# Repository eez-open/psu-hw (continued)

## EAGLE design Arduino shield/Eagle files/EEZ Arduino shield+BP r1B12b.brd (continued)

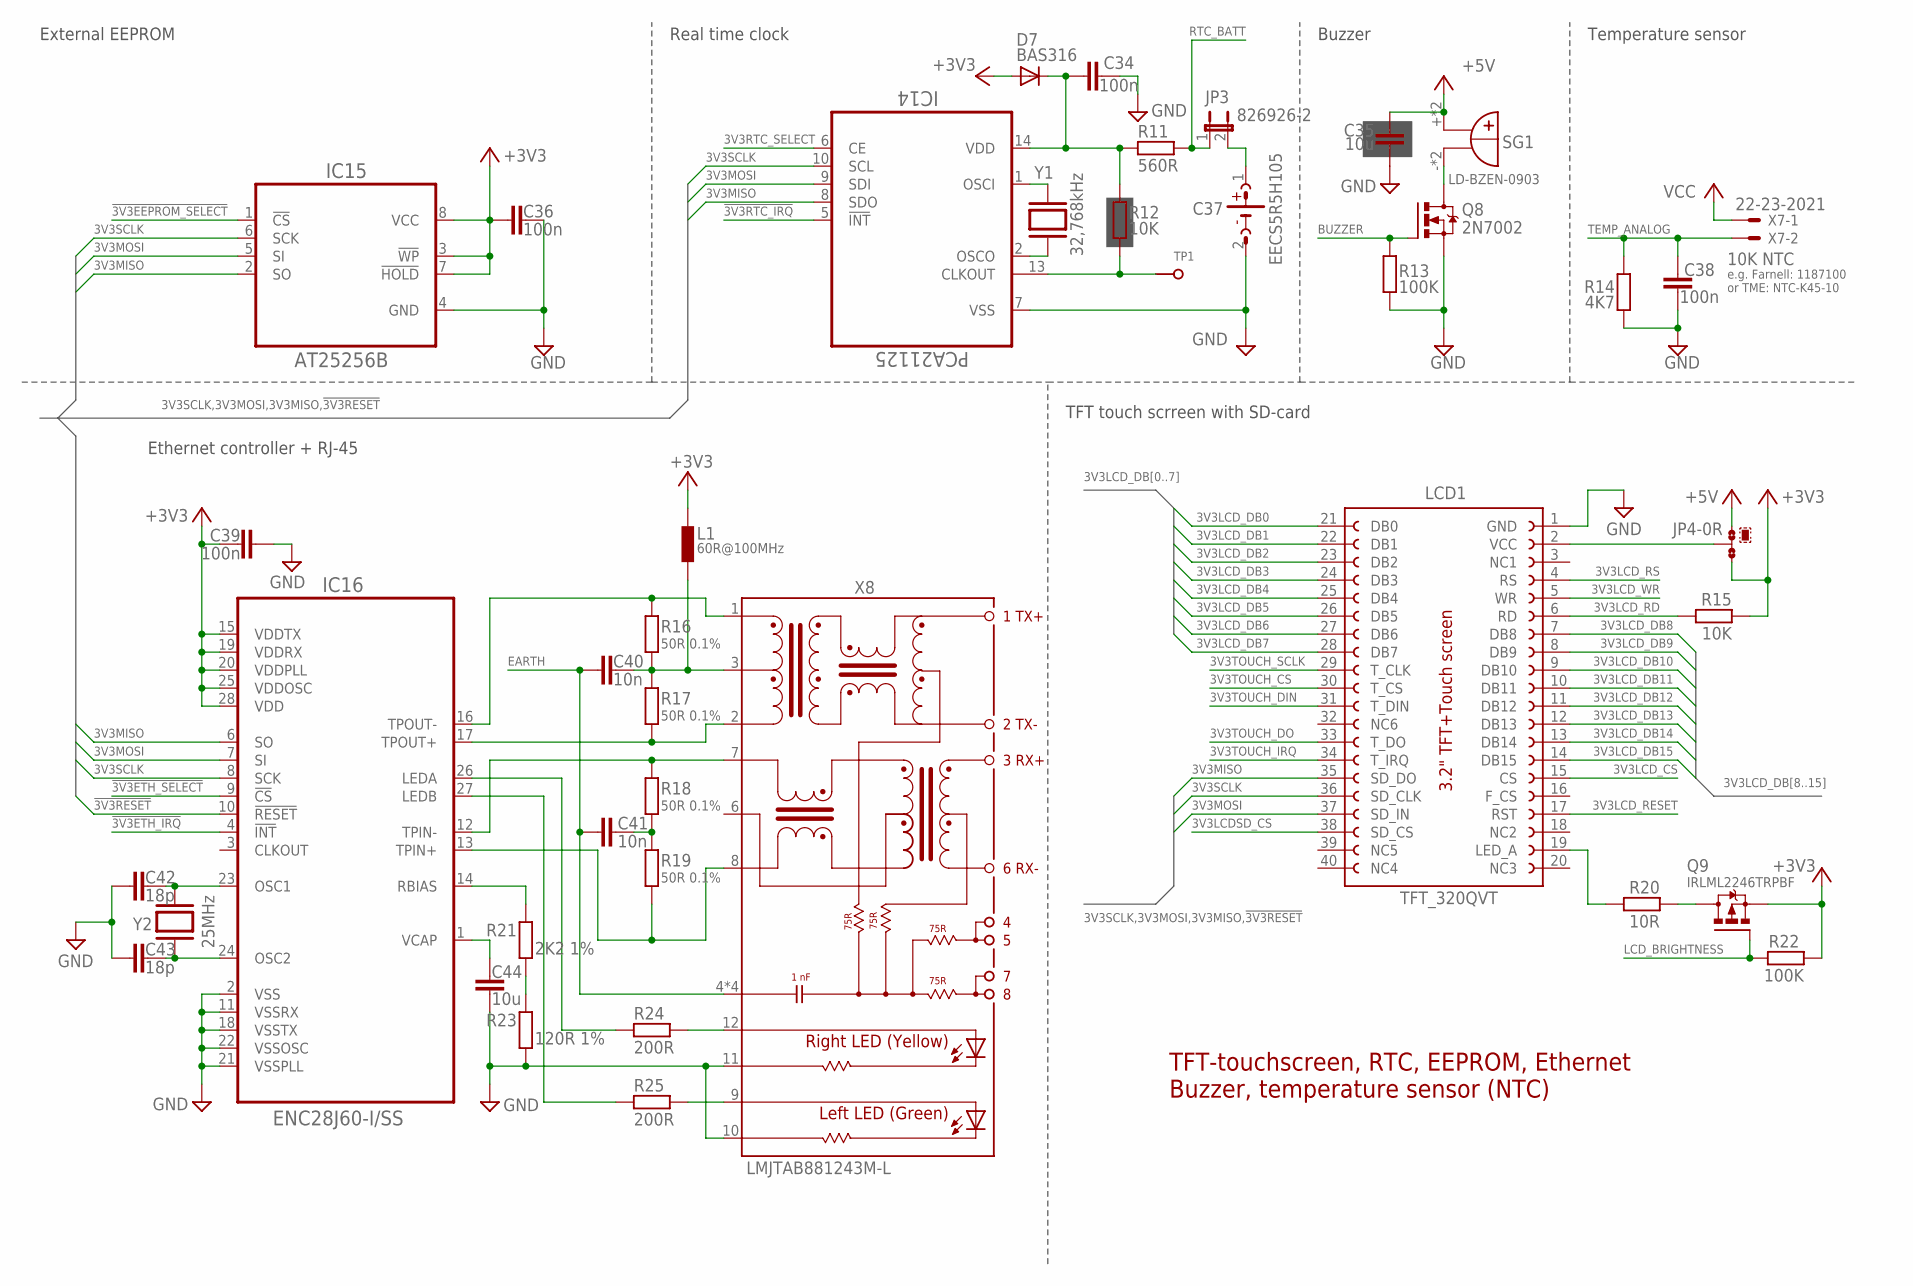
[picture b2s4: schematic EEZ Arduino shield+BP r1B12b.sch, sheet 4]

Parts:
C34, C36, C38, C39: 100n; C0603
C35, C44: 10u; C1206
C37: EECS5R5H105; SG-R20MM
C40, C41: 10n; C1206
C42, C43: 18p; C0805
D7: BAS316; SOD323-W
IC14: PCA21125; SOP65P640X120-14N
IC15: AT25256B; SOIC127P600X175-8N
IC16: ENC28J60-I/SS; SOP65P780X200-28N
JP3: 826926-2; JP1
JP4: 0R-JUMPA; A0R-JMP
L1: 60R@100MHz; BEAD0603
LCD1: TFT_320QVT; LCD_TFT_320QVT_MIRROR
Q8: 2N7002; SOT103P240X110-3N
Q9: IRLML2246TRPBF; SOT95P237X112-3N
R11: 560R; R0805
R12, R15: 10K; R0805
R13, R22: 100K; R0805
R14: 4K7; R0805
R16, R17, R18, R19: 50R 0.1%; R0805
R20: 10R; R0805
R21: 2K2 1%; R0805
R23: 120R 1%; R0805
R24, R25: 200R; R0805
SG1: LD-BZEN-0903; BUZZER
TP1: PCB_TEST_TABSHIELD; PCB_SHIELD_TAB
X7: 22-23-2021; MPN 22-23-2021
X8: LMJTAB881243M-L; RJ45-TRAFO-LED
Y1: 32,768kHz; R26_XTAL
Y2: 25MHz; HC-49/4H

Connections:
3V3LCDSD_CS: LCD1.38 (SD_CS); also elsewhere on the board
3V3LCD_CS: LCD1.15 (CS); also elsewhere on the board
3V3LCD_DB0: LCD1.21 (DB0); also elsewhere on the board
3V3LCD_DB1: LCD1.22 (DB1); also elsewhere on the board
3V3LCD_DB2: LCD1.23 (DB2); also elsewhere on the board
3V3LCD_DB3: LCD1.24 (DB3); also elsewhere on the board
3V3LCD_DB4: LCD1.25 (DB4); also elsewhere on the board
3V3LCD_DB5: LCD1.26 (DB5); also elsewhere on the board
3V3LCD_DB6: LCD1.27 (DB6); also elsewhere on the board
3V3LCD_DB7: LCD1.28 (DB7); also elsewhere on the board
3V3LCD_DB8: LCD1.7 (DB8); also elsewhere on the board
3V3LCD_DB9: LCD1.8 (DB9); also elsewhere on the board
3V3LCD_DB10: LCD1.9 (DB10); also elsewhere on the board
3V3LCD_DB11: LCD1.10 (DB11); also elsewhere on the board
3V3LCD_DB12: LCD1.11 (DB12); also elsewhere on the board
3V3LCD_DB13: LCD1.12 (DB13); also elsewhere on the board
3V3LCD_DB14: LCD1.13 (DB14); also elsewhere on the board
3V3LCD_DB15: LCD1.14 (DB15); also elsewhere on the board
3V3LCD_RD: LCD1.6 (RD), R15.1
3V3LCD_RESET: LCD1.17 (RST); also elsewhere on the board
3V3LCD_RS: LCD1.4 (RS); also elsewhere on the board
3V3LCD_WR: LCD1.5 (WR); also elsewhere on the board
3V3MISO: IC14.8 (SDO), IC15.2 (SO), IC16.6 (SO), LCD1.35 (SD_DO); also elsewhere on the board
3V3MOSI: IC14.9 (SDI), IC15.5 (SI), IC16.7 (SI), LCD1.37 (SD_IN); also elsewhere on the board
3V3RTC_SELECT: IC14.6 (CE); also elsewhere on the board
3V3SCLK: IC14.10 (SCL), IC15.6 (SCK), IC16.8 (SCK), LCD1.36 (SD_CLK); also elsewhere on the board
3V3TOUCH_CS: LCD1.30 (T_CS); also elsewhere on the board
3V3TOUCH_DIN: LCD1.31 (T_DIN); also elsewhere on the board
3V3TOUCH_DO: LCD1.33 (T_DO); also elsewhere on the board
3V3TOUCH_IRQ: LCD1.34 (T_IRQ); also elsewhere on the board
3V3TOUCH_SCLK: LCD1.29 (T_CLK); also elsewhere on the board
!3V3EEPROM_SELECT: IC15.1 (!CS); also elsewhere on the board
!3V3ETH_IRQ: IC16.4 (!INT); also elsewhere on the board
!3V3ETH_SELECT: IC16.9 (!CS); also elsewhere on the board
!3V3RESET: IC16.10 (!RESET); also elsewhere on the board
!3V3RTC_IRQ: IC14.5 (!INT); also elsewhere on the board
+3V3: C36.1, C39.1, D7.A, IC15.3 (!WP), IC15.7 (!HOLD), IC15.8 (VCC), IC16.15 (VDDTX), IC16.19 (VDDRX), IC16.20 (VDDPLL), IC16.25 (VDDOSC), IC16.28 (VDD), JP4.3, L1.P$2 (2), Q9.2 (S), R15.2, R22.2; also elsewhere on the board
+5V: C35.2, JP4.1, SG1.+, SG1.+B (+); also elsewhere on the board
BUZZER: Q8.1 (G), R13.2; also elsewhere on the board
EARTH: C40.2, C41.2, X8.4 (SH), X8.5 (SH), X8.SH1 (SH), X8.SH2 (SH); also elsewhere on the board
ETH_IN+: IC16.13 (TPIN+), R19.1, X8.8 (RD-)
ETH_IN-: IC16.12 (TPIN-), R18.2, X8.7 (RD+)
ETH_LEDA: IC16.26 (LEDA), R24.1
ETH_LEDB: IC16.27 (LEDB), R25.1
ETH_OUT+: IC16.17 (TPOUT+), R17.1, X8.2 (TD-)
ETH_OUT-: IC16.16 (TPOUT-), R16.2, X8.1 (TD+)
GND: C34.1, C35.1, C36.2, C37.2 (-), C38.1, C39.2, C42.2, C43.2, C44.1, IC14.7 (VSS), IC15.4 (GND), IC16.2 (VSS), IC16.11 (VSSRX), IC16.18 (VSSTX), IC16.21 (VSSPLL), IC16.22 (VSSOSC), LCD1.1 (GND), Q8.2 (S), R13.1, R14.2, R23.2, X8.10 (GREEN-C), X8.11 (YELLOW-C); also elsewhere on the board
LCD_BRIGHTNESS: Q9.1 (G), R22.1; also elsewhere on the board
LED_A: LCD1.19 (LED_A), R20.2
unnamed: JP4.2, LCD1.2 (VCC)
unnamed: Q9.3 (D), R20.1
unnamed: IC14.1 (OSCI), Y1.2
unnamed: IC14.2 (OSCO), Y1.1
unnamed: R21.2, R23.1
unnamed: Q8.3 (D), SG1.-, SG1.-B (-)
unnamed: IC14.13 (CLKOUT), R12.2, TP1.1
unnamed: C37.1 (+), JP3.2
unnamed: C42.1, IC16.23 (OSC1), Y2.2
unnamed: C43.1, IC16.24 (OSC2), Y2.1
unnamed: C44.2, IC16.1 (VCAP)
unnamed: IC16.14 (RBIAS), R21.1
unnamed: C34.2, D7.C, IC14.14 (VDD), R11.2, R12.1
unnamed: R24.2, X8.12 (YELLOW_A)
unnamed: R25.2, X8.9 (GREEN-A)
unnamed: C41.1, R18.1, R19.2
unnamed: C40.1, L1.P$1 (1), R16.1, R17.2, X8.3 (CT)
RTC_BATT: JP3.1, R11.1; also elsewhere on the board
TEMP_ANALOG: C38.2, R14.1, X7.2; also elsewhere on the board
VCC: X7.1; also elsewhere on the board

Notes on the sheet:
TFT-touchscreen, RTC, EEPROM, Ethernet
e.g. Farnell: 1187100
10K NTC
or TME: NTC-K45-10
Buzzer, temperature sensor (NTC)
External EEPROM
Real time clock
Buzzer
Temperature sensor
TFT touch scrreen with SD-card
Ethernet controller + RJ-45

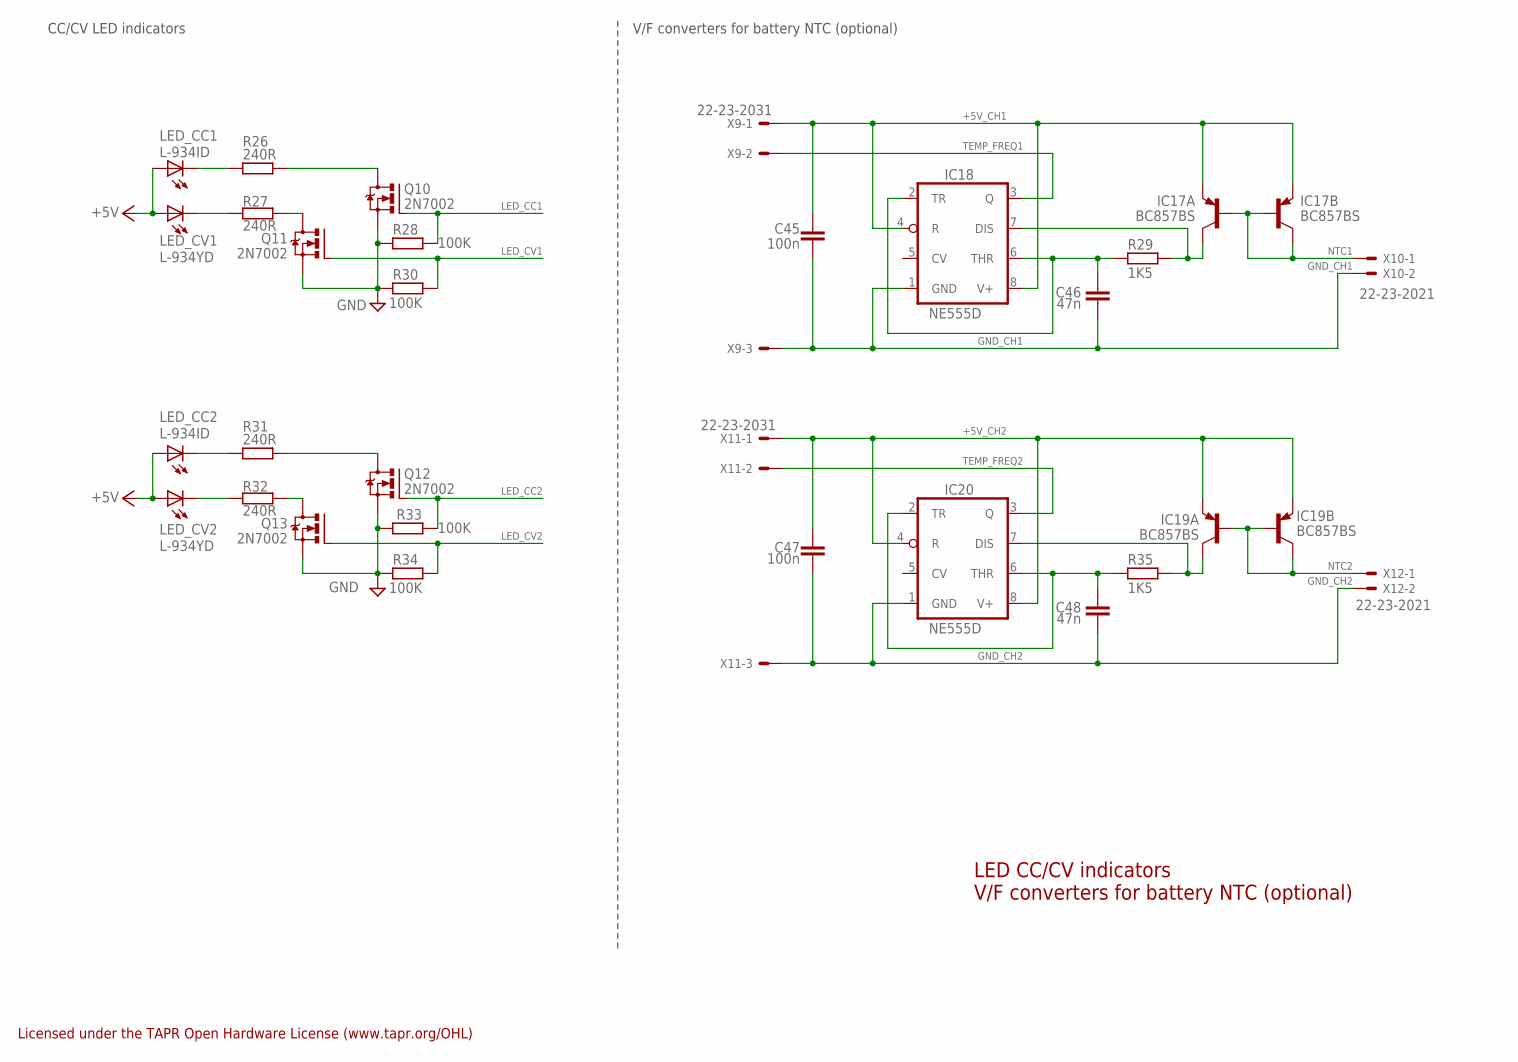
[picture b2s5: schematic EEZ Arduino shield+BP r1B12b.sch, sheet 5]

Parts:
C45, C47: 100n; C0603
C46, C48: 47n; C0805
IC17, IC19: BC857BS; SOT65P210X110-6N
IC18, IC20: NE555D; SOIC127P600X175-8N
LED_CC1, LED_CC2: L-934ID; LED3MM
LED_CV1, LED_CV2: L-934YD; LED3MM
Q10: 2N7002; SOT103P240X110-3N
Q11, Q12, Q13: 2N7002; SOT103P240X110-3N; MPN 2N7002-7-F
R26, R27, R31, R32: 240R; R0805
R28, R30, R33, R34: 100K; R0805
R29, R35: 1K5; R0805
X9, X11: 22-23-2031; MPN 22-23-2031
X10, X12: 22-23-2021

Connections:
+5V: LED_CC1.A, LED_CC2.A, LED_CV1.A, LED_CV2.A; also elsewhere on the board
+5V_CH1: C45.1, IC17.1 (E), IC17.4 (E), IC18.4 (R), IC18.8 (V+), X9.1
+5V_CH2: C47.1, IC19.1 (E), IC19.4 (E), IC20.4 (R), IC20.8 (V+), X11.1
GND: Q10.2 (S), Q11.2 (S), Q12.2 (S), Q13.2 (S), R28.2, R30.2, R33.2, R34.2; also elsewhere on the board
GND_CH1: C45.2, C46.1, IC18.1 (GND), X9.3, X10.2
GND_CH2: C47.2, C48.1, IC20.1 (GND), X11.3, X12.2
LED_CC1: Q10.1 (G), R28.1; also elsewhere on the board
LED_CC2: Q12.1 (G), R33.1; also elsewhere on the board
LED_CV1: Q11.1 (G), R30.1; also elsewhere on the board
LED_CV2: Q13.1 (G), R34.1; also elsewhere on the board
unnamed: LED_CV1.K (C), R27.2
unnamed: Q12.3 (D), R31.2
unnamed: LED_CV2.K (C), R32.2
unnamed: LED_CC2.K (C), R31.1
unnamed: C46.2, IC18.2 (TR), IC18.6 (THR), R29.2
unnamed: IC19.6 (C), IC20.7 (DIS), R35.1
unnamed: IC17.6 (C), IC18.7 (DIS), R29.1
unnamed: C48.2, IC20.2 (TR), IC20.6 (THR), R35.2
unnamed: Q10.3 (D), R26.2
unnamed: Q13.3 (D), R32.1
unnamed: Q11.3 (D), R27.1
unnamed: LED_CC1.K (C), R26.1
NTC1: IC17.2 (B), IC17.3 (C), IC17.5 (B), X10.1
NTC2: IC19.2 (B), IC19.3 (C), IC19.5 (B), X12.1
TEMP_FREQ1: IC18.3 (Q), X9.2
TEMP_FREQ2: IC20.3 (Q), X11.2

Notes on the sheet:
V/F converters for battery NTC (optional)
LED CC/CV indicators
CC/CV LED indicators
Licensed under the TAPR Open Hardware License (www.tapr.org/OHL)

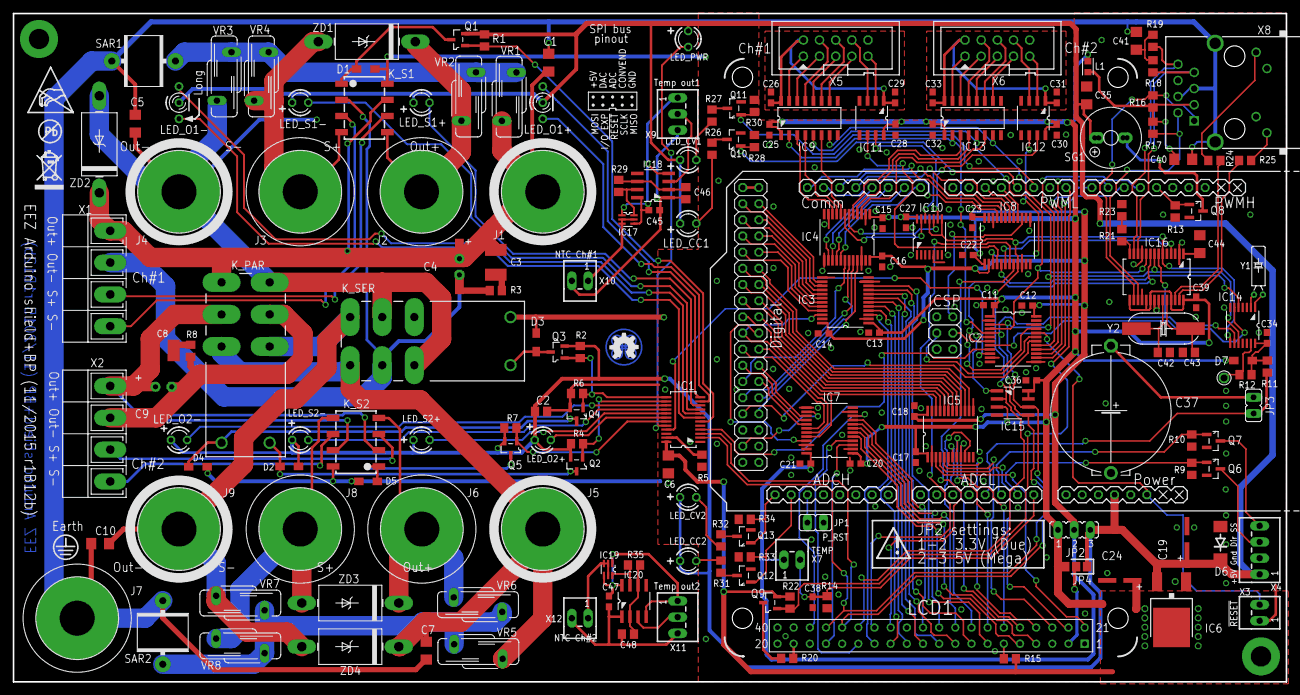
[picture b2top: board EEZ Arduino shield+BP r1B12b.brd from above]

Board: 3 copper layers, 200.0 x 105.0 mm, 191 parts (1 on the bottom side), 220 nets.

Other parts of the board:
EEZ_SIGNATURE: SIGNATURESMALL; SIGNATURE_5MM
U$2: RECYCLE_BIN1/8
U$3: PB_SMALL
U$4: ESD_SYMBOL

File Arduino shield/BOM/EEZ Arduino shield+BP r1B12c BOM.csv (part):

Partlist exported from /home/denis/BACKUP/Home/Audio/DIY v2/PCB/Projects/Programmable PSU/Old versions/Arduino shield/EEZ Arduino shield+BP r1B13.sch at 27. 03. 2016. 14:21

Assembly variant: 

Qty Value                Device                  Parts                                                                                                                                     
1                        ARDUINO_MEGA+ICSPMIRROR MCU                                                                                                                                       
1                        PCB_TEST_TABSHIELD      TP1                                                                                                                                       
1   0R-JUMPA             0R-JUMPA                JP4                                                                                                                                       
2   1K                   R-EU_R0805              R42, R43                                                                                                                                  
5   1K5                  R-EU_R0805              R5, R29, R32, R37, R39                                                                                                                    
2   1R                   R-EU_R0805              R2, R8                                                                                                                                    
1   1u                   C-EUC0805               C3                                                                                                                                        
1   2K2 1%               R-EU_R0805              R21                                                                                                                                       
8   2N7002               2N7002                  Q4, Q6, Q7, Q8, Q10, Q11, Q12, Q13                                                                                                        
4   4K7                  R-EU_R0805              R1, R3, R7, R14                                                                                                                           
1   4V3                  ZENER-DIODEMINIMELF     ZD5                                                                                                                                       
2   10K                  R-EU_R0805              R12, R15                                                                                                                                  
1   10K                  R-EU_R1206              R41                                                                                                                                       
1   10R                  R-EU_R0805              R20                                                                                                                                       
6   10n                  C-EUC1206               C1, C5, C7, C10, C40, C41                                                                                                                 
3   10u                  C-EUC1206               C6, C35, C44                                                                                                                              
1   10u                  ECAPPANASONIC_C         C24                                                                                                                                       
2   18p                  C-EUC0805               C42, C43                                                                                                                                  
4   22-23-2021           22-23-2021              X5, X9, X11, X12                                                                                                                          
1   22-23-2041           22-23-2041              X6                                                                                                                                        
2   22u/63V              ECAPEEEFK+2.5MM         C4, C9                                                                                                                                    
1   25MHz                XTALSMD                 Y2                                                                                                                                        
1   32,768kHz            XTALR26                 Y1                                                                                                                                        
2   47n                  C-EUC0805               C46, C48                                                                                                                                  
1   47u                  ECAPPANASONIC_C         C19                                                                                                                                       
4   49R9                 R-EU_R0805              R16, R17, R18, R19                                                                                                                        
2   60R@100MHz           FERRITE_BEAD0603        FB, L1                                                                                                                                    
10  100K                 R-EU_R0805              R4, R6, R9, R10, R13, R22, R28, R31, R35, R36                                                                                             
1   100R                 R-EU_R0805              R40                                                                                                                                       
28  100n                 C-EUC0603               C11, C12, C13, C14, C15, C16, C17, C18, C20, C21, C22, C23, C25, C26, C27, C28, C29, C30, C31, C32, C33, C34, C36, C38, C39, C45, C47, C49
1   120R 1%              R-EU_R0805              R23                                                                                                                                       
2   180R                 R-EU_R0805              R30, R38                                                                                                                                  
2   200R                 R-EU_R0805              R24, R25                                                                                                                                  
4   240R                 R-EU_R0805              R26, R27, R33, R34                                                                                                                        
2   470n/100V            C-EUC1812               C2, C8                                                                                                                                    
1   560R                 R-EU_R0805              R11                                                                                                                                       
1   1301.9316            TACT_SW                 SW1                                                                                                                                       
2   282836-4             TBLOCK5.0_4A            X1, X3                                                                                                                                    
2   826926-2             JP1E                    JP1, JP3                                                                                                                                  
1   826926-3             JUMPER_3-PIN            JP2                                                                                                                                       
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
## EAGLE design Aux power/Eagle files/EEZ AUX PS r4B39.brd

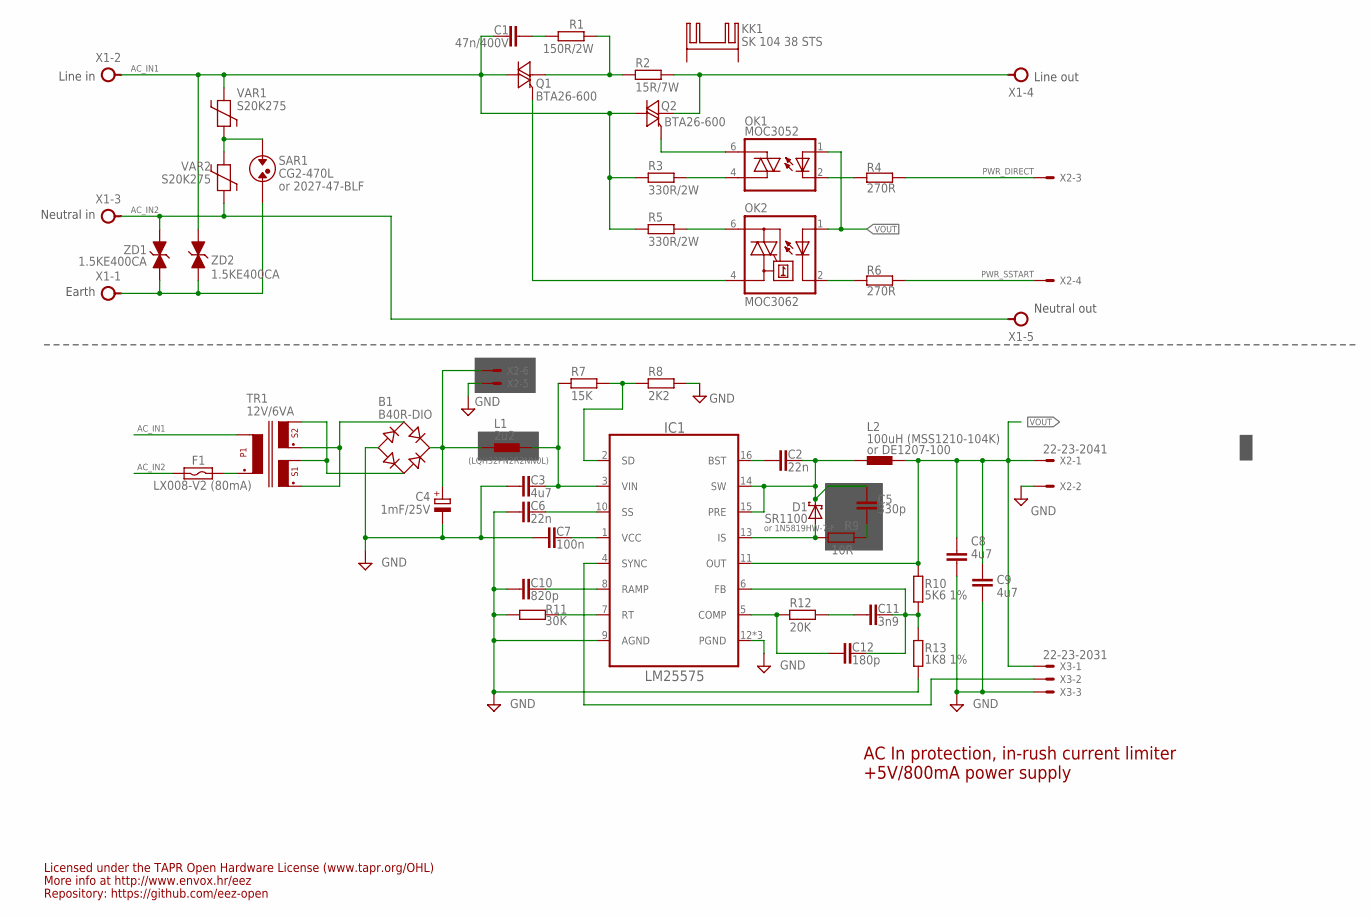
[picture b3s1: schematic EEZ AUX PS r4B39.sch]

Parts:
B1: B40R-DIO; RB1A
C1: 47n/400V; C075-052X106
C2, C6: 22n; C0805
C3, C8, C9: 4u7; C1210
C4: 1mF/25V; ECAP5/10.5
C5: 330p; C0805
C7: 100n; C0805
C10: 820p; C0805
C11: 3n9; C0805
C12: 180p; C0805
D1: SR1100; DO34+SOD123
F1: LX008-V2 (80mA); POLYSWITCH-R7
IC1: LM25575; SOP65P640X110-17N_HOLE
KK1: SK 104 38 STS; SK409
L1: 2u2; L1210
L2: 100uH (MSS1210-104K); MSS1278
OK1: MOC3052; DIL6-SMD
OK2: MOC3062; DIL6-SMD; MPN MOC3033S-M
Q1, Q2: BTA26-600; TOP3S-1
R1: 150R/2W; R2512
R2: 15R/7W; R_0913
R3, R5: 330R/2W; R2512
R4, R6: 270R; R0805
R7: 15K; R0805
R8: 2K2; R0805
R9: 10R; R1206
R10: 5K6 1%; R0805
R11: 30K; R0805
R12: 20K; R0805
R13: 1K8 1%; R0805
SAR1: CG2-470L; SAR
TR1: 12V/6VA; PCB_TRAFO6VA_DUAL
VAR1, VAR2: S20K275; VARISTOR
X1: AC_IN; TBLOCK5.0_5
X2: 22-23-2041; 22-23-2061; MPN 22-23-2061
X3: 22-23-2031
ZD1, ZD2: 1.5KE400CA; DO201-BIDIR

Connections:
AC_EARTH: SAR1.P$2, X1.1, ZD1.C (1), ZD2.C (1)
AC_IN1: C1.2, Q1.A2, Q2.A2, R3.2, R5.2, TR1.NC1 (P1), TR1.P1, TR1.P1.1 (P1), TR1.P1.2 (P1), VAR1.P$2, X1.2, ZD2.A (2)
AC_IN2: F1.P$1 (1), VAR2.P$1, X1.3, X1.5, ZD1.A (2)
DC_PREG1: C3.1, IC1.3 (VIN), L1.2, R7.2
GND: B1.-, C3.2, C4.-, C6.2, C7.1, C8.2, C9.2, C10.1, IC1.9 (AGND), IC1.12 (PGND), IC1.TP (PGND), IC1.TP2 (PGND), R8.1, R11.2, R13.2, X2.2, X2.5, X3.3
IS: D1.A, D1.A.1 (A), IC1.13 (IS), R9.1
unnamed: C5.2, R9.2
unnamed: OK1.6 (A2), Q2.G
unnamed: OK1.4 (A1), R3.1
unnamed: OK2.4 (A1), Q1.G
unnamed: OK1.2 (C), R4.1
unnamed: OK2.2 (C), R6.1
unnamed: OK2.6 (A2), R5.1
unnamed: Q2.A1, R2.2, X1.4
unnamed: IC1.4 (SYNC), X3.2
unnamed: C1.1, R1.1
unnamed: Q1.A1, R1.2, R2.1
unnamed: B1.AC2, TR1.S1.2, TR1.S1.2A (S1.2), TR1.S1.2NC (S1.2), TR1.S2.2
unnamed: C11.2, R12.2
unnamed: SAR1.P$1, VAR1.P$1, VAR2.P$2
unnamed: C11.1, C12.1, IC1.6 (FB), R10.2, R13.1
unnamed: C2.2, IC1.16 (BST)
unnamed: C12.2, IC1.5 (COMP), R12.1
unnamed: B1.AC1, TR1.S1.1, TR1.S2.1, TR1.S2.1A (S2.1)
unnamed: F1.P$2 (2), TR1.P2, TR1.P2.1 (P2), TR1.P2.2 (P2)
unnamed: IC1.7 (RT), R11.1
unnamed: C7.2, IC1.1 (VCC)
unnamed: C10.2, IC1.8 (RAMP)
unnamed: C6.1, IC1.10 (SS)
unnamed: IC1.2 (SD), R7.1, R8.2
PWR_DIRECT: R4.2, X2.3
PWR_SSTART: R6.2, X2.4
SW: C2.1, C5.1, D1.C, D1.C.1 (C), IC1.14 (SW), IC1.15 (PRE), L2.1
VIN: B1.+, C4.+, L1.1, X2.6
VOUT: C8.1, C9.1, IC1.11 (OUT), L2.2, OK1.1 (A), OK2.1 (A), R10.1, X2.1, X3.1

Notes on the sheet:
AC In protection, in-rush current limiter
+5V/800mA power supply
Line in
Neutral in
Earth
or DE1207-100
or 1N5819HW-7-F
Line out
Neutral out
or 2027-47-BLF
(LQH32PN2R2NN0L)
Repository: https://github.com/eez-open
Licensed under the TAPR Open Hardware License (www.tapr.org/OHL)
More info at http://www.envox.hr/eez

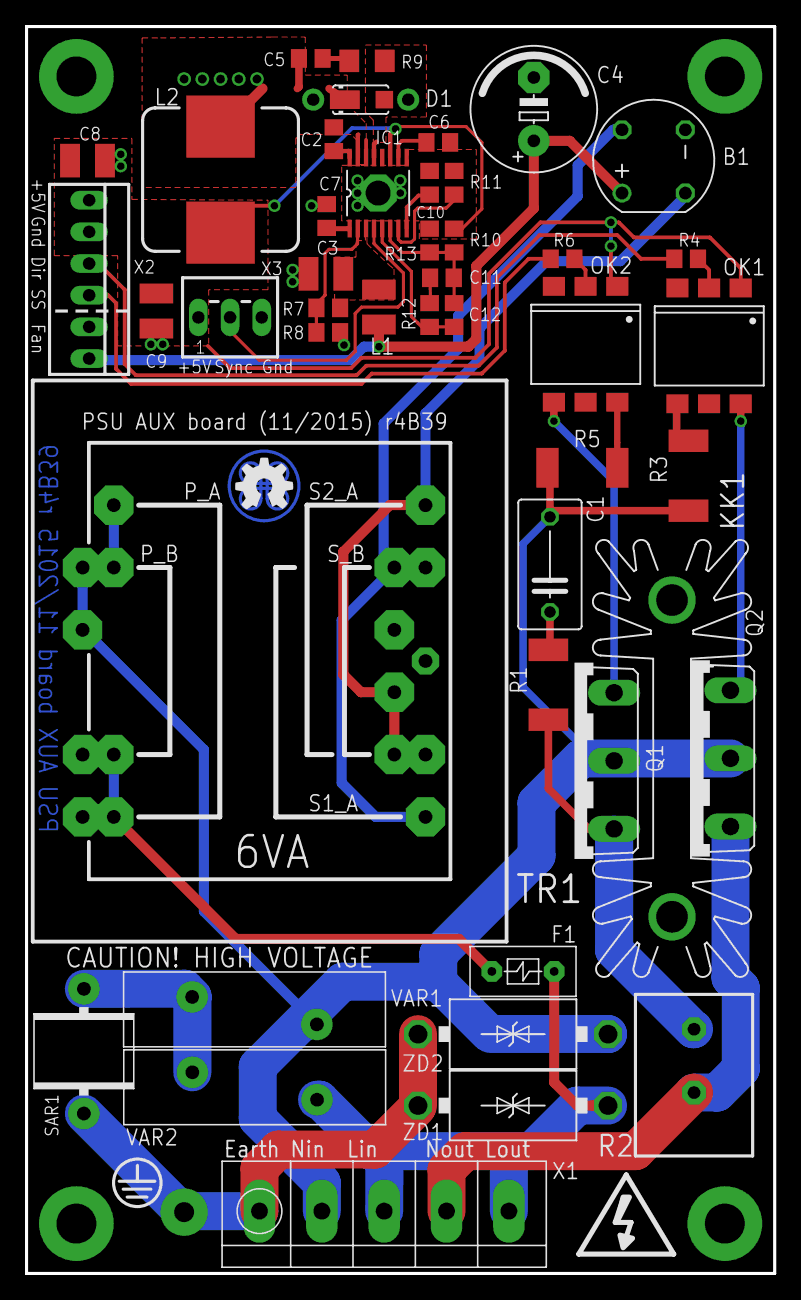
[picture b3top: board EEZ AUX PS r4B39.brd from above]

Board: 3 copper layers, 60.0 x 100.0 mm, 46 parts (0 on the bottom side), 35 nets.

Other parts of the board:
EEZ_SIGNATURE: SIGNATURESMALL; SIGNATURE_5MM

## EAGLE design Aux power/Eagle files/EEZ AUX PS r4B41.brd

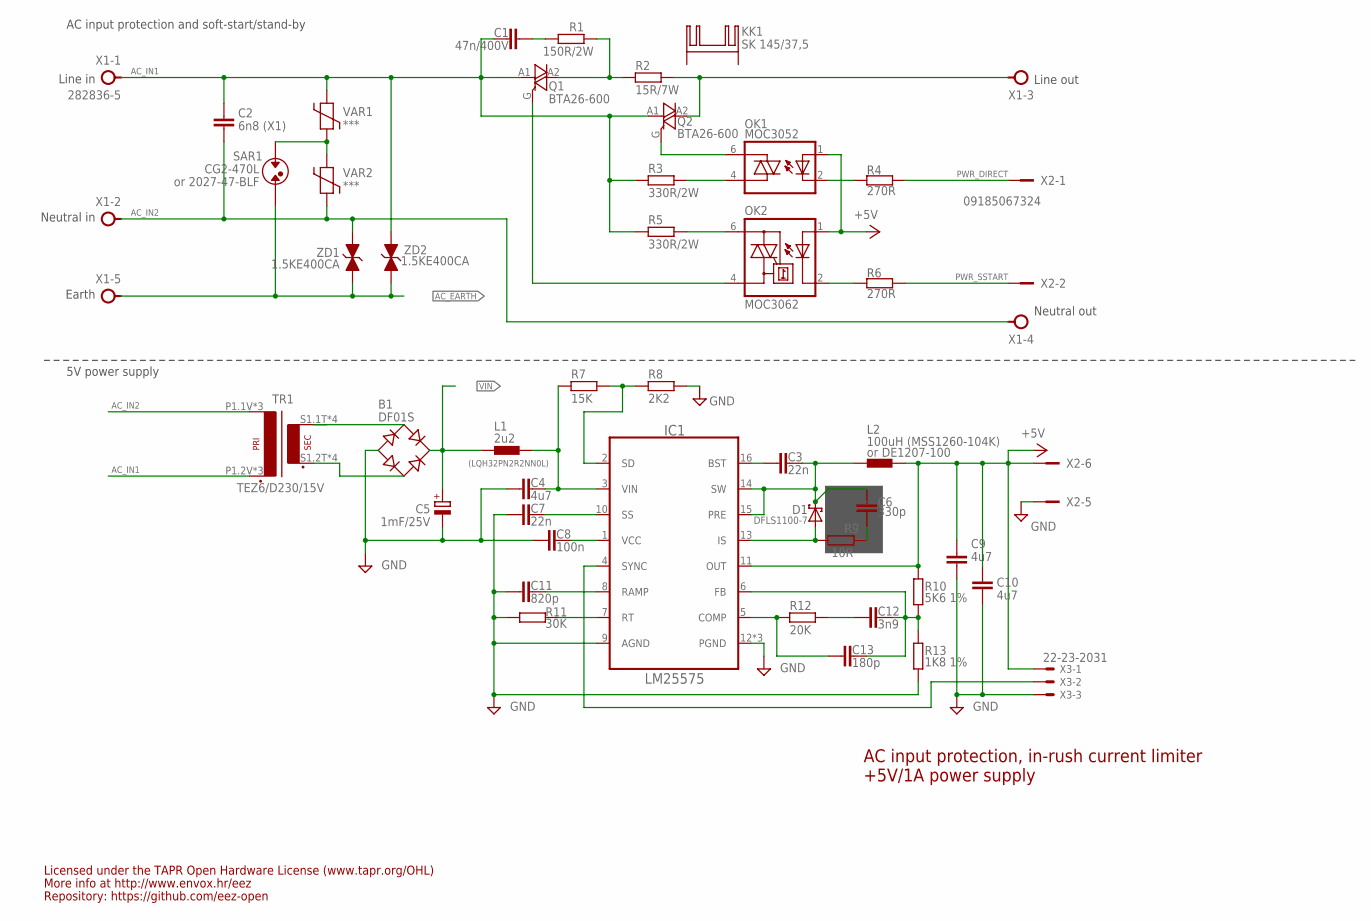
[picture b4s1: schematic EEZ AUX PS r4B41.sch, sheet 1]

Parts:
B1: DF01S; DFS
C1: 47n/400V; C075-052X106
C2: 6n8 (X1); C102-064X133
C3, C7: 22n; C0805
C4, C9, C10: 4u7; C1210
C5: 1mF/25V; ECAP5/10.5
C6: 330p; C0805
C8: 100n; C0805
C11: 820p; C0805
C12: 3n9; C0805
C13: 180p; C0805
D1: DFLS1100-7; SOD123
IC1: LM25575; SOP65P640X110-17N_HOLE
KK1: SK 145/37,5; SK145
L1: 2u2; L1210
L2: 100uH (MSS1260-104K); MSS1278
OK1: MOC3052; DIL6-SMD
OK2: MOC3062; DIL6-SMD; MPN MOC3033S-M
Q1, Q2: BTA26-600; TOP3S-1
R1: 150R/2W; R2512
R2: 15R/7W; R_0913
R3, R5: 330R/2W; R2512
R4, R6: 270R; R0805
R7: 15K; R0805
R8: 2K2; R0805
R9: 10R; R1206
R10: 5K6 1%; R0805
R11: 30K; R0805
R12: 20K; R0805
R13: 1K8 1%; R0805
SAR1: CG2-470L; SAR
TR1: TEZ6/D230/15V; PCB_TRAFO6VA_TEZ+VPP
VAR1, VAR2: ***; VARISTOR
X1: 282836-5; TBLOCK5.0_5
X2: 09185067324; IDC-6PIN
X3: 22-23-2031
ZD1, ZD2: 1.5KE400CA; DO201-BIDIR

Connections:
+5V: C9.1, C10.1, IC1.11 (OUT), L2.2, OK1.1 (A), OK2.1 (A), R10.1, X2.6, X3.1; also elsewhere on the board
AC_EARTH: SAR1.P$2, X1.5, ZD1.C (1), ZD2.C (1)
AC_IN1: C1.2, C2.1, Q1.A1, Q2.A1, R3.2, R5.2, TR1.P1.2V (P2), TR1.P2.2V (P2), TR1.P2_TEZ (P2), VAR1.P$2, X1.1, ZD2.A (2)
AC_IN2: C2.2, TR1.P1.1V (P1), TR1.P1_TEZ (P1), TR1.P2.1V (P1), VAR2.P$1, X1.2, X1.4, ZD1.A (2)
DC_PREG1: C4.1, IC1.3 (VIN), L1.2, R7.2
GND: B1.-, C4.2, C5.-, C7.2, C8.1, C9.2, C10.2, C11.1, IC1.9 (AGND), IC1.12 (PGND), IC1.TP (PGND), IC1.TP2 (PGND), R8.1, R11.2, R13.2, X2.5, X3.3; also elsewhere on the board
IS: D1.A, IC1.13 (IS), R9.1
unnamed: C6.2, R9.2
unnamed: OK1.6 (A2), Q2.G
unnamed: OK1.4 (A1), R3.1
unnamed: OK2.4 (A1), Q1.G
unnamed: OK1.2 (C), R4.1
unnamed: OK2.2 (C), R6.1
unnamed: OK2.6 (A2), R5.1
unnamed: Q2.A2, R2.2, X1.3
unnamed: B1.AC1, TR1.S1.1T (S1), TR1.S1.1V (S1), TR1.S2.1T (S1), TR1.S2.1V (S1)
unnamed: IC1.4 (SYNC), X3.2
unnamed: C1.1, R1.1
unnamed: B1.AC2, TR1.S1.2T (S2), TR1.S1.2V (S2), TR1.S2.2T (S2), TR1.S2.2V (S2)
unnamed: Q1.A2, R1.2, R2.1
unnamed: C12.2, R12.2
unnamed: SAR1.P$1, VAR1.P$1, VAR2.P$2
unnamed: C12.1, C13.1, IC1.6 (FB), R10.2, R13.1
unnamed: C3.2, IC1.16 (BST)
unnamed: C13.2, IC1.5 (COMP), R12.1
unnamed: IC1.7 (RT), R11.1
unnamed: C8.2, IC1.1 (VCC)
unnamed: C11.2, IC1.8 (RAMP)
unnamed: C7.1, IC1.10 (SS)
unnamed: IC1.2 (SD), R7.1, R8.2
PWR_DIRECT: R4.2, X2.1
PWR_SSTART: R6.2, X2.2
SW: C3.1, C6.1, D1.C, IC1.14 (SW), IC1.15 (PRE), L2.1
VIN: B1.+, C5.+, L1.1; also elsewhere on the board

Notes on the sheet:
AC input protection, in-rush current limiter
+5V/1A power supply
Line in
Neutral in
Earth
or DE1207-100
Line out
Neutral out
or 2027-47-BLF
(LQH32PN2R2NN0L)
Licensed under the TAPR Open Hardware License (www.tapr.org/OHL)
Repository: https://github.com/eez-open
More info at http://www.envox.hr/eez
5V power supply
AC input protection and soft-start/stand-by

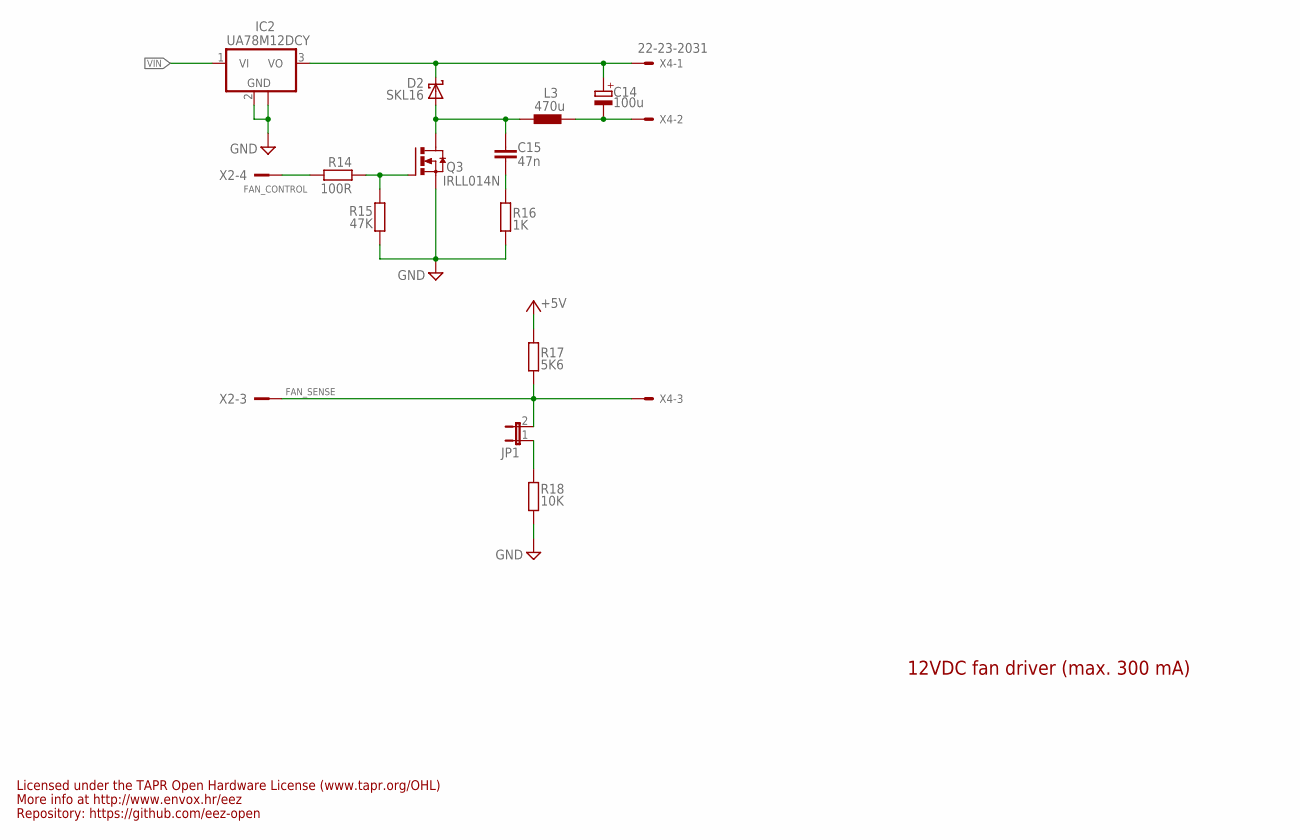
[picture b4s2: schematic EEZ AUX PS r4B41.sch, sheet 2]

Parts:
C14: 100u; CAPAE660X610N
C15: 47n; C0805
D2: SKL16; SOD123
IC2: UA78M12DCY; SOT230P700X180-4N
JP1: JP1E; JP1
L3: 470u; DE0704
Q3: IRLL014N; SOT223
R14: 100R; R0805
R15: 47K; R0805
R16: 1K; R0805
R17: 5K6; R0805
R18: 10K; R0805
X2: 09185067324; IDC-6PIN
X4: 22-23-2031

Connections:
+5V: R17.1; also elsewhere on the board
FAN_CONTROL: R14.2, X2.4
FAN_OUT: C15.2, D2.A, L3.2, Q3.2 (D), Q3.4 (D)
FAN_SENSE: JP1.2, R17.2, X2.3, X4.3
GND: IC2.2 (GND), IC2.4 (GND), Q3.3 (S), R15.1, R16.1, R18.2; also elsewhere on the board
unnamed: JP1.1, R18.1
unnamed: C15.1, R16.2
unnamed: Q3.1 (G), R14.1, R15.2
unnamed: C14.1 (+), D2.C, IC2.3 (VO), X4.1
unnamed: C14.2 (-), L3.1, X4.2
VIN: IC2.1 (VI); also elsewhere on the board

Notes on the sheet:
12VDC fan driver (max. 300 mA)
Licensed under the TAPR Open Hardware License (www.tapr.org/OHL)
Repository: https://github.com/eez-open
More info at http://www.envox.hr/eez
